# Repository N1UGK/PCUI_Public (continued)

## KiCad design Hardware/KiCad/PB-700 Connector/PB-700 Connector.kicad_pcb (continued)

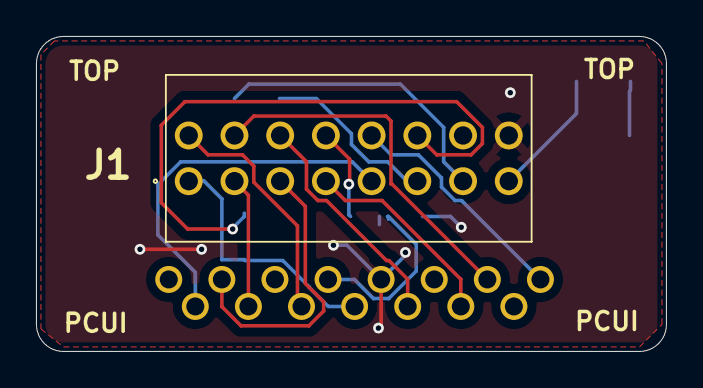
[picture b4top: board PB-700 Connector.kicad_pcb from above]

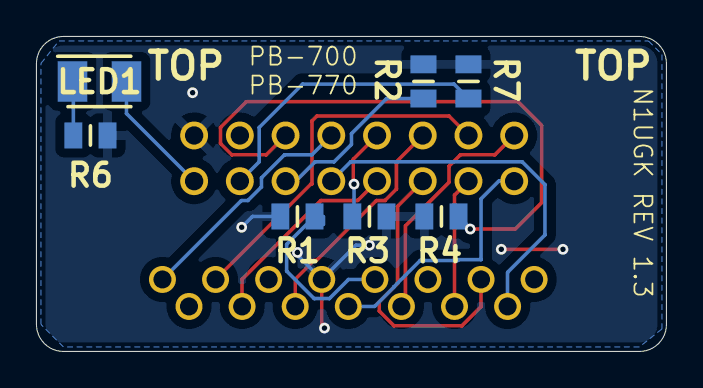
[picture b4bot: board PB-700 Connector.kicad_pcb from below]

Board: 2 copper layers, 35.0 x 17.5 mm, 23 parts (22 on the bottom side), 17 nets.

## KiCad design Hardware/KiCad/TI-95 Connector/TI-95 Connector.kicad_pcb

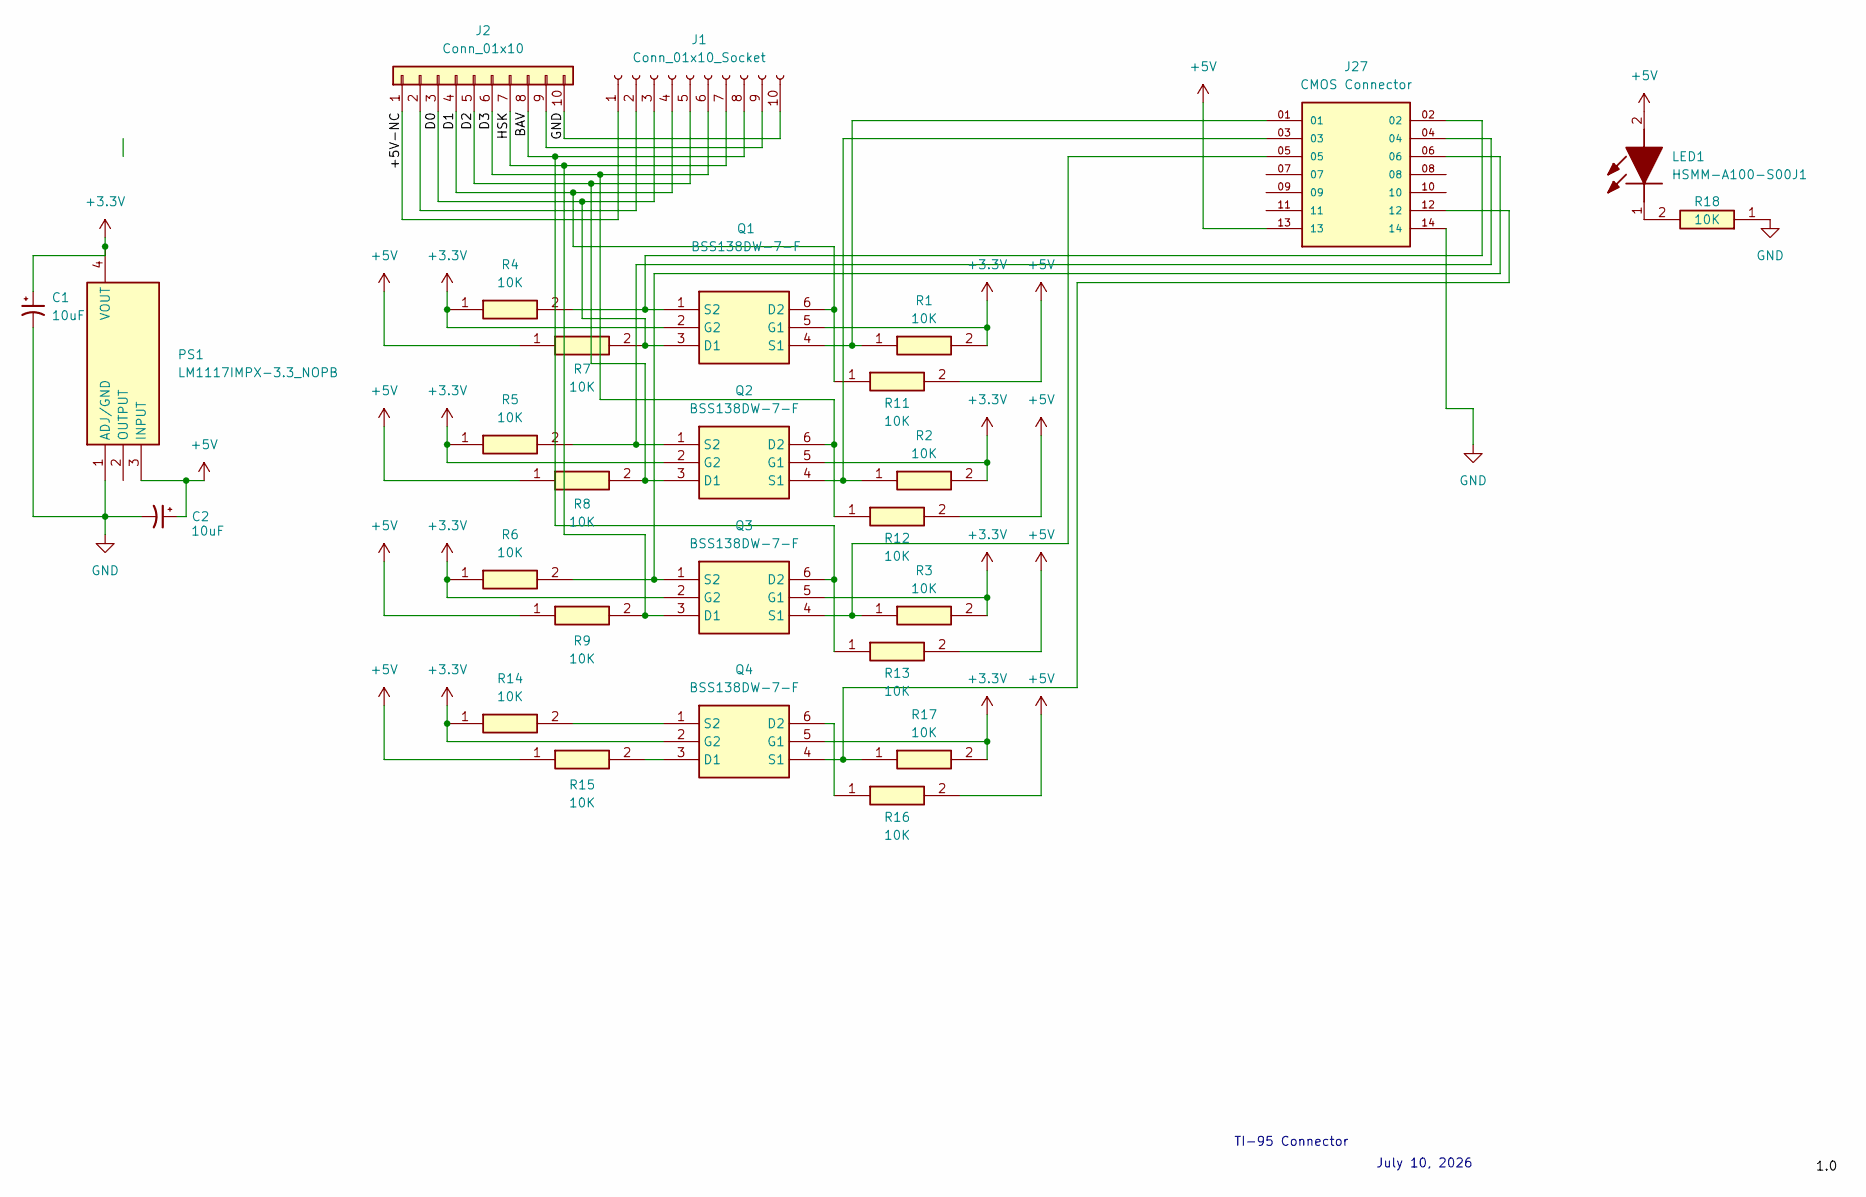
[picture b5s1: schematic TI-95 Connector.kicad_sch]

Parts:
C1, C2: 10uF; CP_EIA-3528-15_AVX-H_HandSolder
J1: Conn_01x10_Socket; PinSocket_1x10_P2.54mm_Vertical
J2: Conn_01x10; PinHeader_1x10_P2.54mm_Vertical
J27: CMOS Connector; SAMTEC_TSS-107-02-H-D; PARTREV R
LED1: HSMM-A100-S00J1; LEDM3528X200N; Mouser Part Number 630-HSMM-A100-S00J1
PS1: LM1117IMPX-3.3_NOPB; SOT230P700X180-4N; Mouser Part Number 926-LM1117IMPX33NOPB
Q1, Q2, Q3, Q4: BSS138DW-7-F; SOT65P210X110-6N; Mouser Part Number 621-BSS138DW-F
R1, R2, R3, R4, R5, R6, R7, R8, R9, R11, R12, R13, R14, R15, R16, R17, R18: 10K; RESC2013X65N; Mouser Part Number 756-WCR0805-10KFI

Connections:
+3.3V: C1.1, PS1.4 (VOUT), Q1.2 (G2), Q1.5 (G1), Q2.2 (G2), Q2.5 (G1), Q3.2 (G2), Q3.5 (G1), Q4.2 (G2), Q4.5 (G1), R1.2, R2.2, R3.2, R4.1, R5.1, R6.1, R14.1, R17.2
+5V: C2.1, J27.13, LED1.2 (A), PS1.3 (INPUT), R7.1, R8.1, R9.1, R11.2, R12.2, R13.2, R15.1, R16.2
/+5V-NC: J1.1, J2.1
/BAV: J1.8, J2.8, Q3.6 (D2), R13.1
/D0: J1.3, J2.3, Q1.3 (D1), R7.2
/D1: J1.4, J2.4, Q1.6 (D2), R11.1
/D2: J1.5, J2.5, Q2.3 (D1), R8.2
/D3: J1.6, J2.6, Q2.6 (D2), R12.1
/HSK: J1.7, J2.7, Q3.3 (D1), R9.2
GND: C1.2, C2.2, J1.10, J2.10, J27.14, PS1.1 (ADJ/GND), R18.1
unnamed: J1.2, J2.2
unnamed: J1.9, J2.9
unnamed: LED1.1 (K), R18.2
unnamed: J27.01, Q1.4 (S1), R1.1
unnamed: J27.02, Q1.1 (S2), R4.2
unnamed: J27.03, Q2.4 (S1), R2.1
unnamed: J27.04, Q2.1 (S2), R5.2
unnamed: J27.05, Q3.4 (S1), R3.1
unnamed: J27.06, Q3.1 (S2), R6.2
unnamed: Q4.3 (D1), R15.2
unnamed: Q4.6 (D2), R16.1
unnamed: J27.12, Q4.4 (S1), R17.1
unnamed: Q4.1 (S2), R14.2

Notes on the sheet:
July 10, 2026
TI-95 Connector

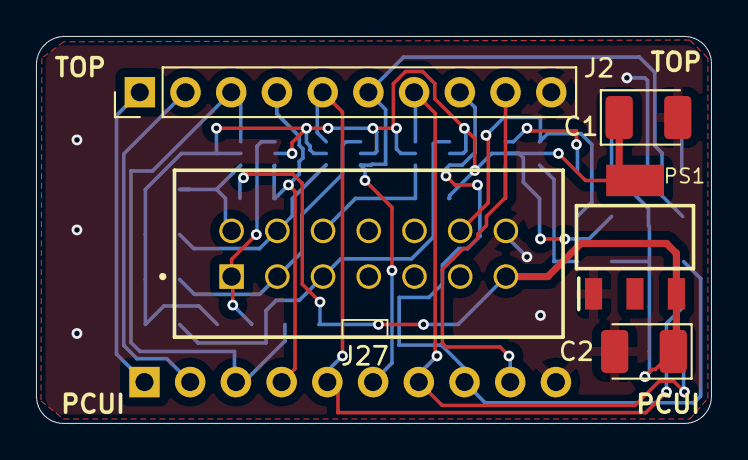
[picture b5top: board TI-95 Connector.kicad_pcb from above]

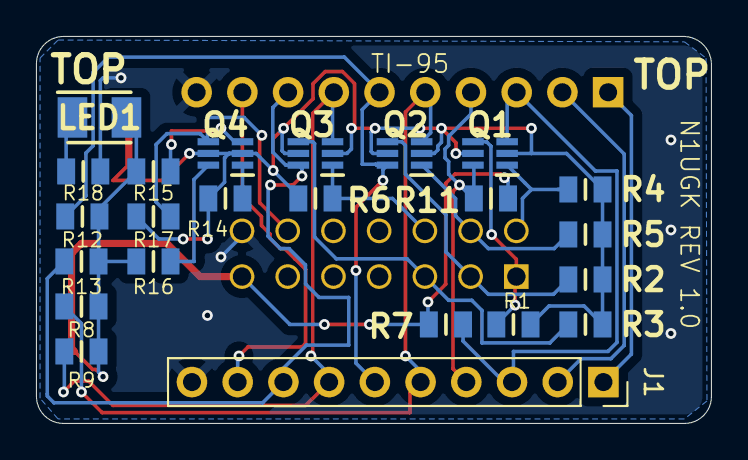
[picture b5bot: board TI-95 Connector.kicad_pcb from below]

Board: 2 copper layers, 37.5 x 21.5 mm, 28 parts (23 on the bottom side), 23 nets.

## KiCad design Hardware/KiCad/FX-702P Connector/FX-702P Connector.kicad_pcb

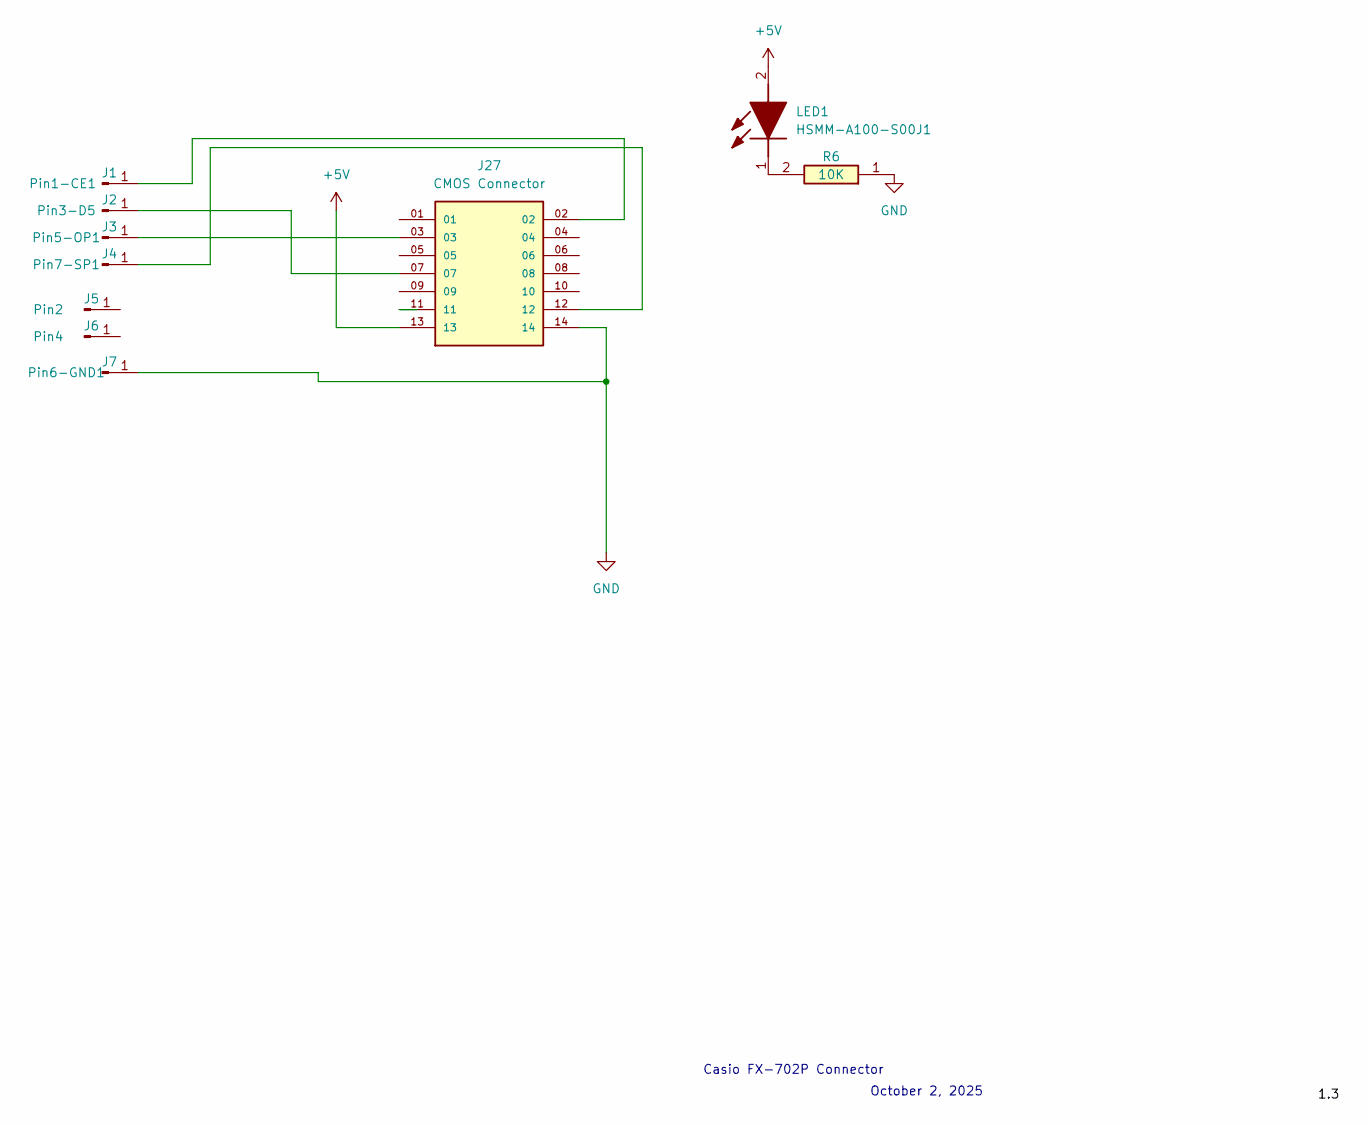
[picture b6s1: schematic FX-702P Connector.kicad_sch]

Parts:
J1: Pin1-CE1; TH_1mm_1.5mm
J2: Pin3-D5; TH_1mm_1.5mm
J3: Pin5-OP1; TH_1mm_1.5mm
J4: Pin7-SP1; TH_1mm_1.5mm
J5: Pin2; TH_1mm_1.5mm
J6: Pin4; TH_1mm_1.5mm
J7: Pin6-GND1; TH_1mm_1.5mm
J27: CMOS Connector; SAMTEC_TSS-107-02-H-D; PARTREV R
LED1: HSMM-A100-S00J1; LEDM3528X200N; Mouser Part Number 630-HSMM-A100-S00J1
R6: 10K; RESC2013X65N; Mouser Part Number 756-WCR0805-10KFI

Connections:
+5V: J27.13, LED1.2 (A)
GND: J7.1, J27.14, R6.1
unnamed: J1.1, J27.02
unnamed: J2.1, J27.07
unnamed: J3.1, J27.03
unnamed: J4.1, J27.12
unnamed: LED1.1 (K), R6.2

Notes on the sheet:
October 2, 2025
Casio FX-702P Connector

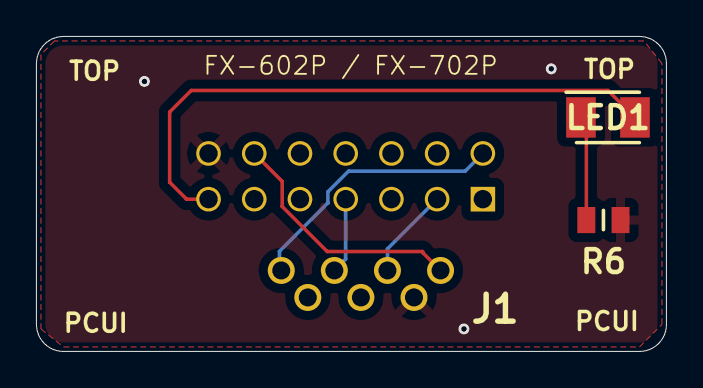
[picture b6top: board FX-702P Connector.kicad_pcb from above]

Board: 2 copper layers, 35.0 x 17.5 mm, 10 parts (1 on the bottom side), 7 nets.

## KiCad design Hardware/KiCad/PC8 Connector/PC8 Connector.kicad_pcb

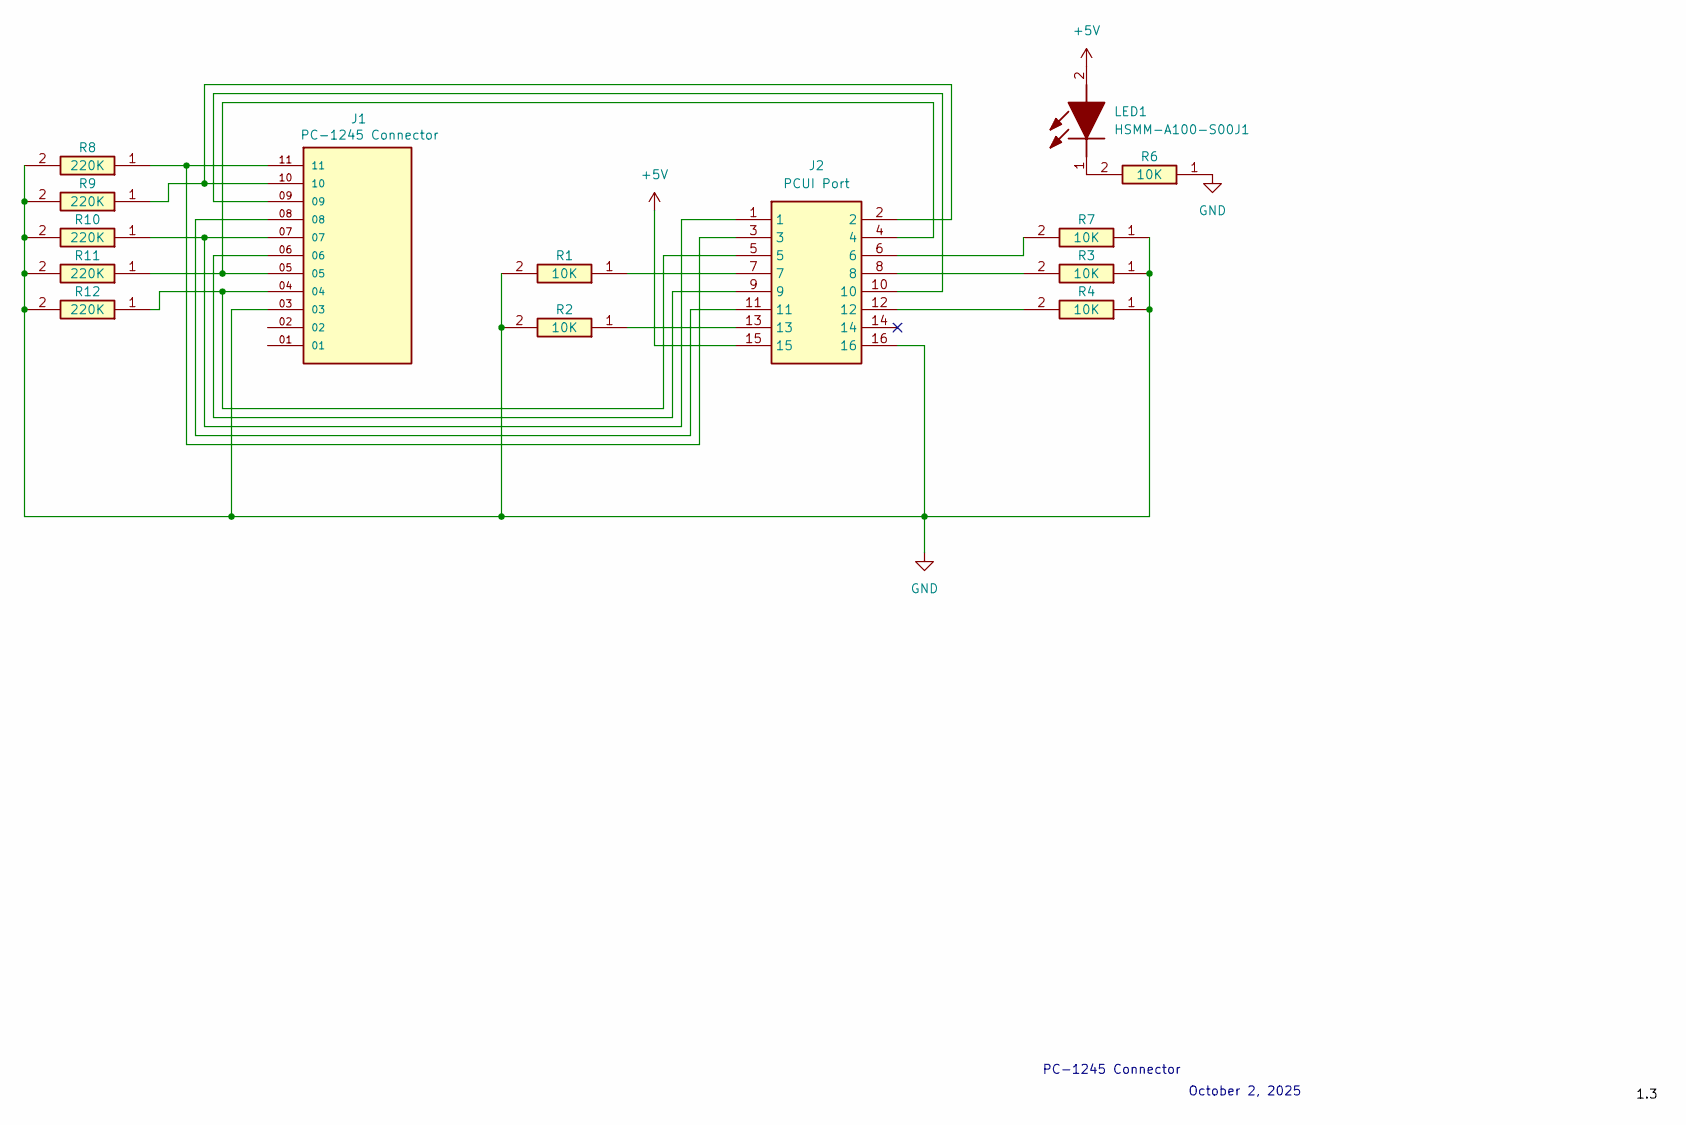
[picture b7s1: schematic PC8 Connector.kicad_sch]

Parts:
J1: PC-1245 Connector; SAMTEC_TSW-111-14-G-S; PARTREV R
J2: PCUI Port; TSS-108-XX-YYY-D; Manufacturer_Part_Number TSS-108-02-L-D
LED1: HSMM-A100-S00J1; LEDM3528X200N; Mouser Part Number 630-HSMM-A100-S00J1
R1, R2, R3, R4, R6, R7: 10K; RESC2013X65N; Mouser Part Number 756-WCR0805-10KFI
R8, R9, R10, R11, R12: 220K; RESC2013X65N; Mouser Part Number 756-WCR0805-10KFI

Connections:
+5V: J2.15, LED1.2 (A); also elsewhere on the board
GND: J1.03, J2.16, R1.2, R2.2, R3.1, R4.1, R6.1, R7.1, R8.2, R9.2, R10.2, R11.2, R12.2
unnamed: J1.04, J2.5, R12.1
unnamed: J1.05, J2.4, R11.1
unnamed: J1.06, J2.9
unnamed: J1.07, J2.1, R10.1
unnamed: J1.08, J2.11
unnamed: J1.09, J2.10
unnamed: J1.10, J2.2, R9.1
unnamed: J1.11, J2.3, R8.1
unnamed: J2.6, R7.2
unnamed: J2.7, R1.1
unnamed: J2.8, R3.2
unnamed: J2.12, R4.2
unnamed: J2.13, R2.1
unnamed 15: LED1.1 (K), R6.2; also elsewhere on the board

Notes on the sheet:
October 2, 2025
PC-1245 Connector

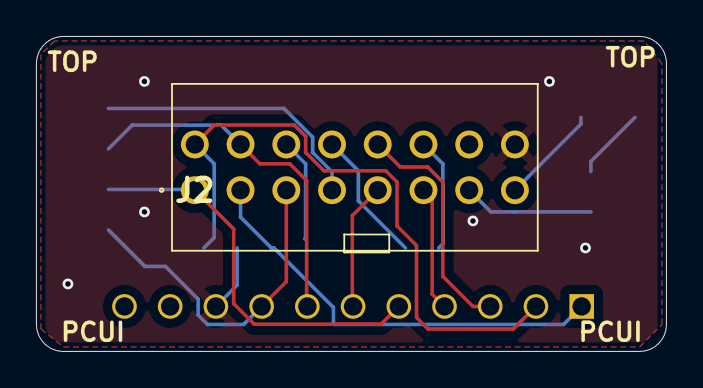
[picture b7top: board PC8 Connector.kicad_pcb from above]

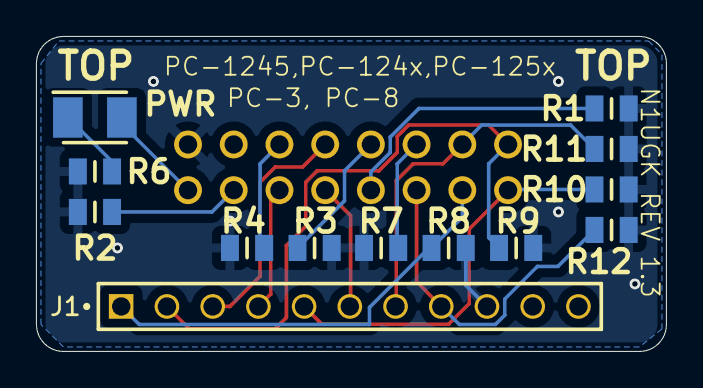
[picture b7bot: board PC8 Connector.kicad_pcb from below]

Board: 2 copper layers, 35.0 x 17.5 mm, 14 parts (13 on the bottom side), 16 nets.

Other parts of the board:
PWR: HSMM-A100-S00J1; LEDM3528X200N

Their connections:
+5V: PWR.2 (A); also elsewhere on the board
unnamed 15: PWR.1 (K); also elsewhere on the board

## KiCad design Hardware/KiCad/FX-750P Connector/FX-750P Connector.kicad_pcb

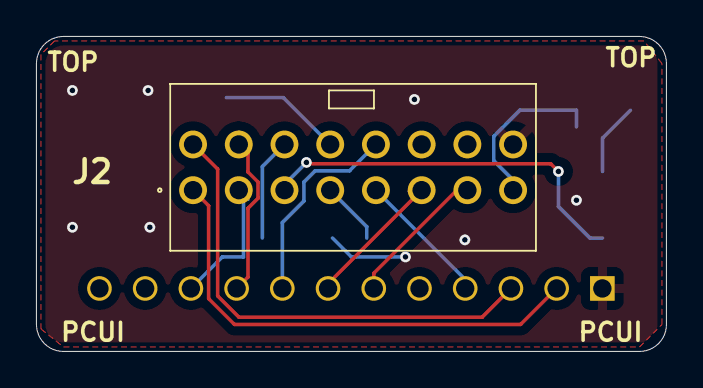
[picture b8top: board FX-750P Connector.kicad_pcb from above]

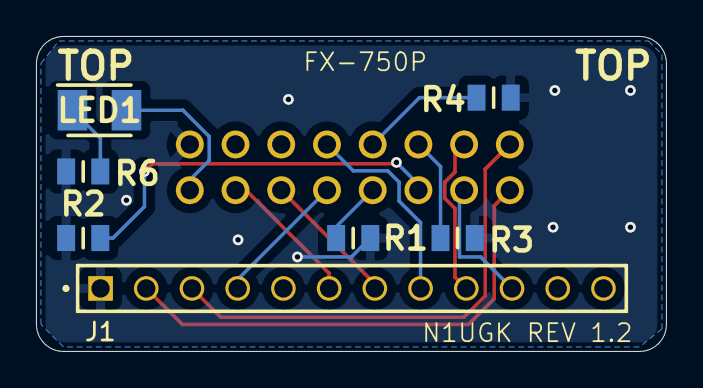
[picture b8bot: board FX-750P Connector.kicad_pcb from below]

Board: 2 copper layers, 35.0 x 17.5 mm, 8 parts (7 on the bottom side), 15 nets.

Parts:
J1: FX-750P Connector; SAMTEC_TSW-112-07-L-S-LL
J2: PCUI Port; TSS-108-XX-YYY-D
LED1: HSMM-A100-S00J1; LEDM3528X200N
R1, R2, R3, R4, R6: 10K; RESC2013X65N

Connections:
+5V: J2.15, LED1.2 (A)
/CE1: J1.03, J2.2
/CE2: J1.02, J2.1
/CK1: J1.10, J2.3
/CK2: J1.09, J2.4
/D1: J1.04, J2.9
/D2: J1.08, J2.10
/D3: J1.07, J2.11
/GPIO11: J2.5, R2.1
/GPIO12: J2.6, R3.2
/GPIO13: J2.7, R1.1
/GPIO14: J2.8, R4.2
/GPIO21: J1.06, J2.13
GND: J1.01, J2.16, R1.2, R2.2, R3.1, R4.1, R6.1
unnamed: LED1.1 (K), R6.2

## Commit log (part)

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2026-05-11 Added first public firmware release and 2 sample programs for the 1401 series.
2026-05-11 Revise README with new title and project details
    Updated project title and added description with image.
2026-05-11 Fix capitalization in project title
    Corrected the capitalization in the project title.
2026-05-21 Added sample programs
2026-05-26 Updated programs and added documentation
2026-06-14 Updated documentation for self-test mode.
2026-06-19 Added owners manuals, organized banner program.
2026-06-20 Remove owners manual link from README
    Removed the link to the PCUI Owners Manual from the README.
2026-06-22 Enhance README with cassette interface information
    Added details about true low-level cassette interface integration.
2026-06-27 Updated documentation
2026-06-28 Organized PB-700 Programs
